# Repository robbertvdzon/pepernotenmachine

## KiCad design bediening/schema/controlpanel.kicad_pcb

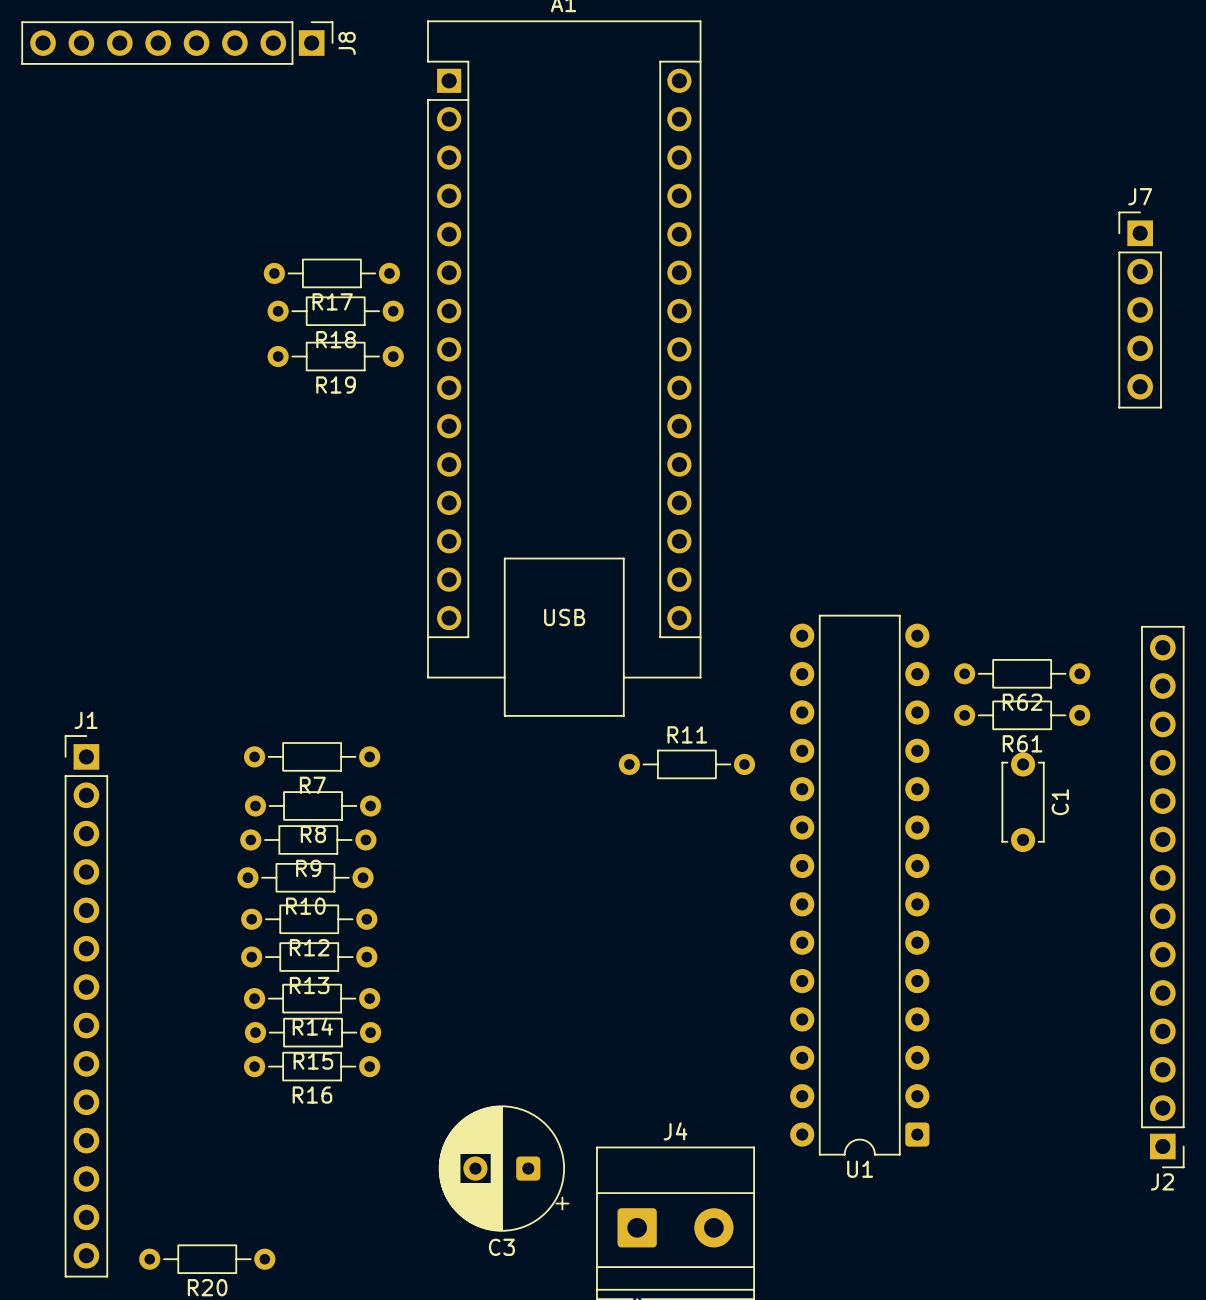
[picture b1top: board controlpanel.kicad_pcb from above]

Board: 2 copper layers, 25 parts (0 on the bottom side), 52 nets, no tracks yet.

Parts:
A1: Arduino_Nano_ESP32; Arduino_Nano
C1: 0.1uF; C_Disc_D5.0mm_W2.5mm_P5.00mm
C3: 470uF; CP_Radial_D8.0mm_P3.50mm
J1: Leds; PinHeader_1x14_P2.54mm_Vertical
J2: Schakelaars; PinHeader_1x14_P2.54mm_Vertical
J4: Power; TerminalBlock_Phoenix_MKDS-1,5-2-5.08_1x02_P5.08mm_Horizont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
J7: Rotary switch; PinHeader_1x05_P2.54mm_Vertical
J8: SPI Display; PinHeader_1x08_P2.54mm_Vertical
R7, R8, R9, R10, R12, R13, R14, R15, R16, R17, R18, R19, R20: 330; R_Axial_DIN0204_L3.6mm_D1.6mm_P7.62mm_Horizontal
R11: 10k; R_Axial_DIN0204_L3.6mm_D1.6mm_P7.62mm_Horizontal
R61, R62: 4k7; R_Axial_DIN0204_L3.6mm_D1.6mm_P7.62mm_Horizontal
U1: MCP23017x-x-SP; DIP-28_W7.62mm

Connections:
+3.3V: A1.17 (3V3), C1.2, R11.1, R61.1, R62.1, U1.9 (V_{DD})
+3V3: J1.13, J2.13, J7.2, J8.8
+5V: A1.30 (VIN), C3.1, J4.2, J8.2
/CS: A1.13 (D10/CS), J8.7
/DC: A1.12 (D9), J8.6
/DISPLAY_RESET: A1.11 (D8), J8.5
/L1: R7.1, U1.21 (GPA0)
/L2: R8.1, U1.22 (GPA1)
/L3: R9.1, U1.23 (GPA2)
/L4: R10.1, U1.24 (GPA3)
/L5: R12.1, U1.25 (GPA4)
/L6: R13.1, U1.26 (GPA5)
/L7: R14.1, U1.27 (GPA6)
/L8: R15.1, U1.28 (GPA7)
/L9: A1.5 (D2), R16.1
/L10: A1.6 (D3), R17.1
/L11: A1.7 (D4), R18.1
/L12: A1.8 (D5), R19.1
/MOSI: A1.14 (D11/COPI), J8.4
/ROT_CLK: A1.19 (A0), J7.4
/ROT_CT: A1.20 (A1), J7.5
/ROT_SW: A1.10 (D7), J7.3
/SCL: A1.24 (SCL/A5), R61.2, U1.12 (SCK)
/SCLK: A1.16 (D13/SCK), J8.3
/SDA: A1.23 (SDA/A4), R62.2, U1.13 (SDA)
/SW1: J2.1, U1.1 (GPB0)
/SW2: J2.2, U1.2 (GPB1)
/SW3: J2.3, U1.3 (GPB2)
/SW4: J2.4, U1.4 (GPB3)
/SW5: J2.5, U1.5 (GPB4)
/SW6: J2.6, U1.6 (GPB5)
/SW7: J2.7, U1.7 (GPB6)
/SW8: J2.8, U1.8 (GPB7)
/SW9: A1.21 (A2), J2.9
/SW10: A1.22 (A3), J2.10
/SW11: A1.25 (A6), J2.11
/SW12: A1.26 (A7), J2.12
GND: A1.4 (GND), A1.29 (GND), C1.1, C3.2, J2.14, J4.1, J7.1, J8.1, R20.1, U1.10 (V_{SS}), U1.15 (A0), U1.16 (A1), U1.17 (A2)
unnamed: J1.1, R7.2
unnamed: J1.2, R8.2
unnamed: J1.3, R9.2
unnamed: J1.4, R10.2
unnamed: J1.5, R12.2
unnamed: J1.6, R13.2
unnamed: J1.7, R14.2
unnamed: J1.8, R15.2
unnamed: J1.9, R16.2
unnamed: J1.10, R17.2
unnamed: J1.11, R18.2
unnamed: J1.12, R19.2
unnamed: J1.14, R20.2
unnamed: R11.2, U1.18 (~RESET)

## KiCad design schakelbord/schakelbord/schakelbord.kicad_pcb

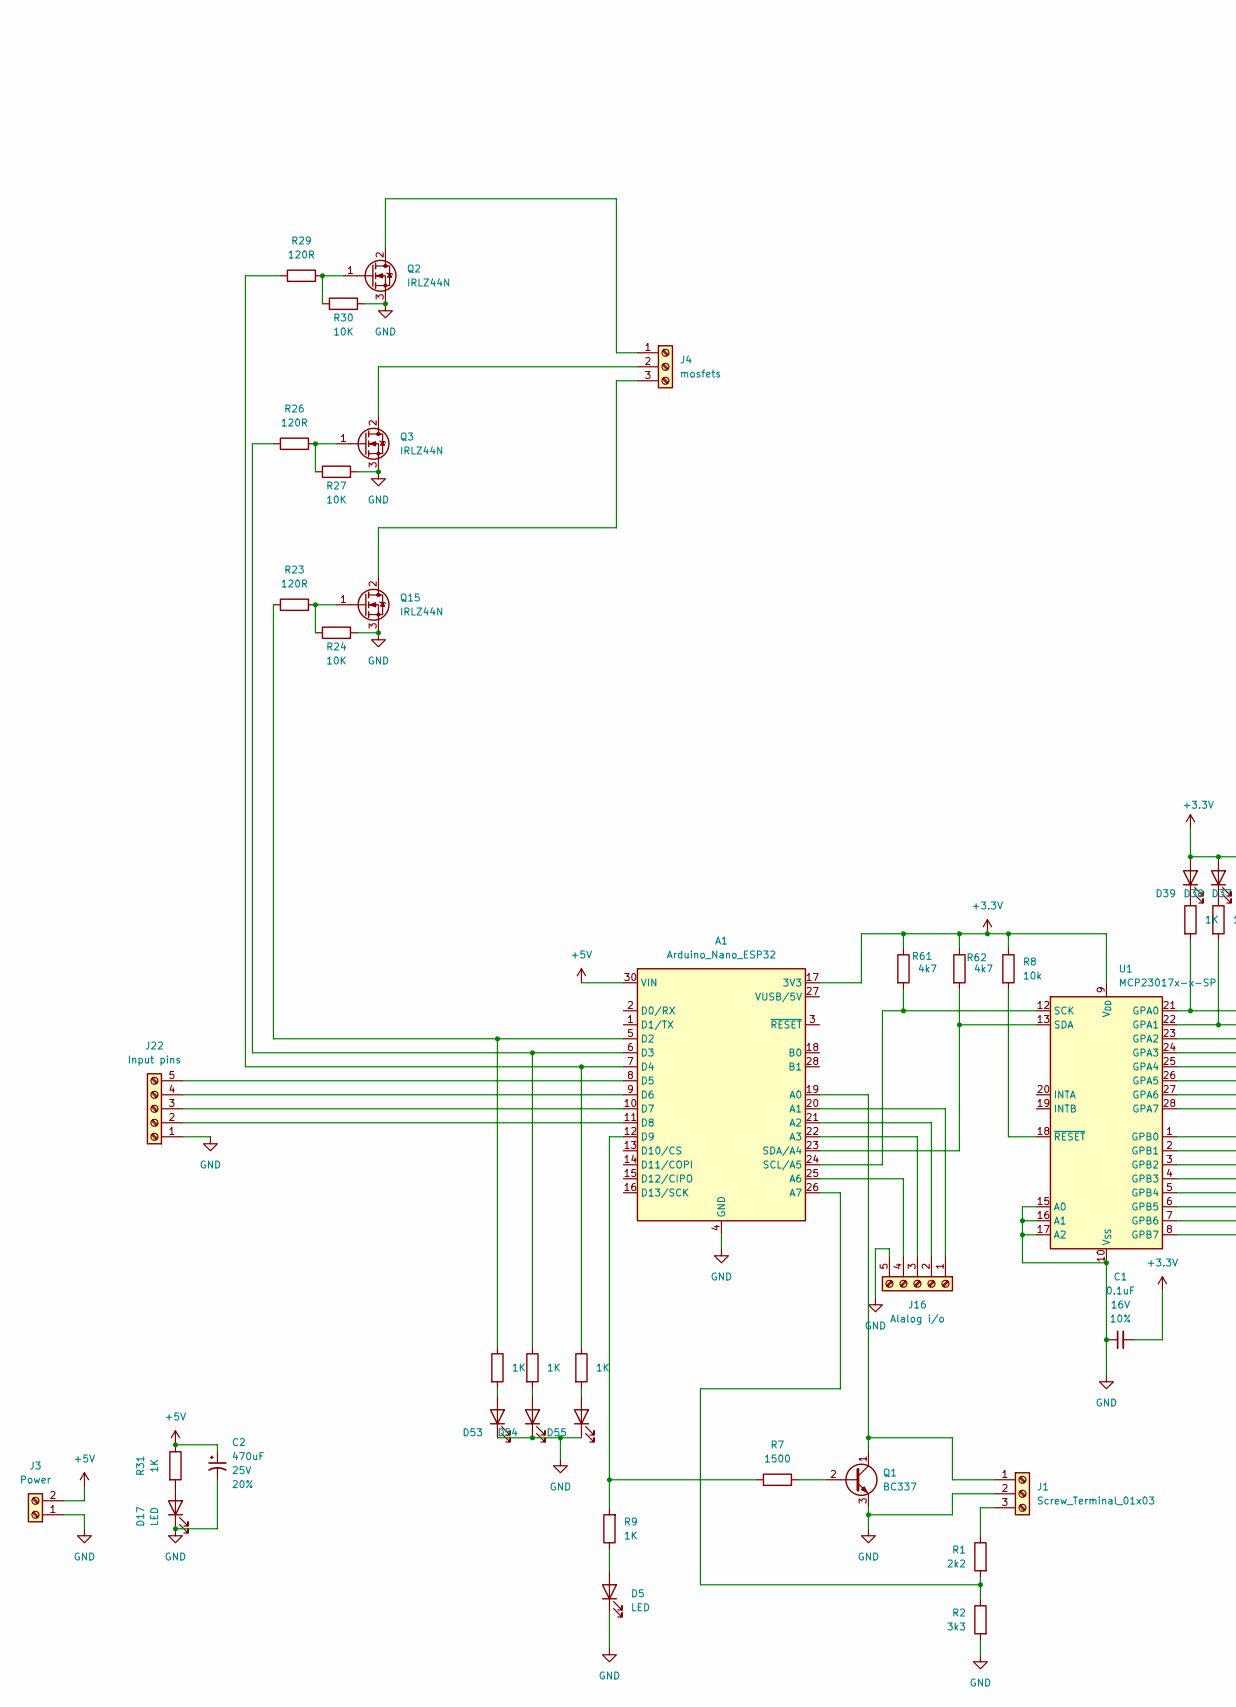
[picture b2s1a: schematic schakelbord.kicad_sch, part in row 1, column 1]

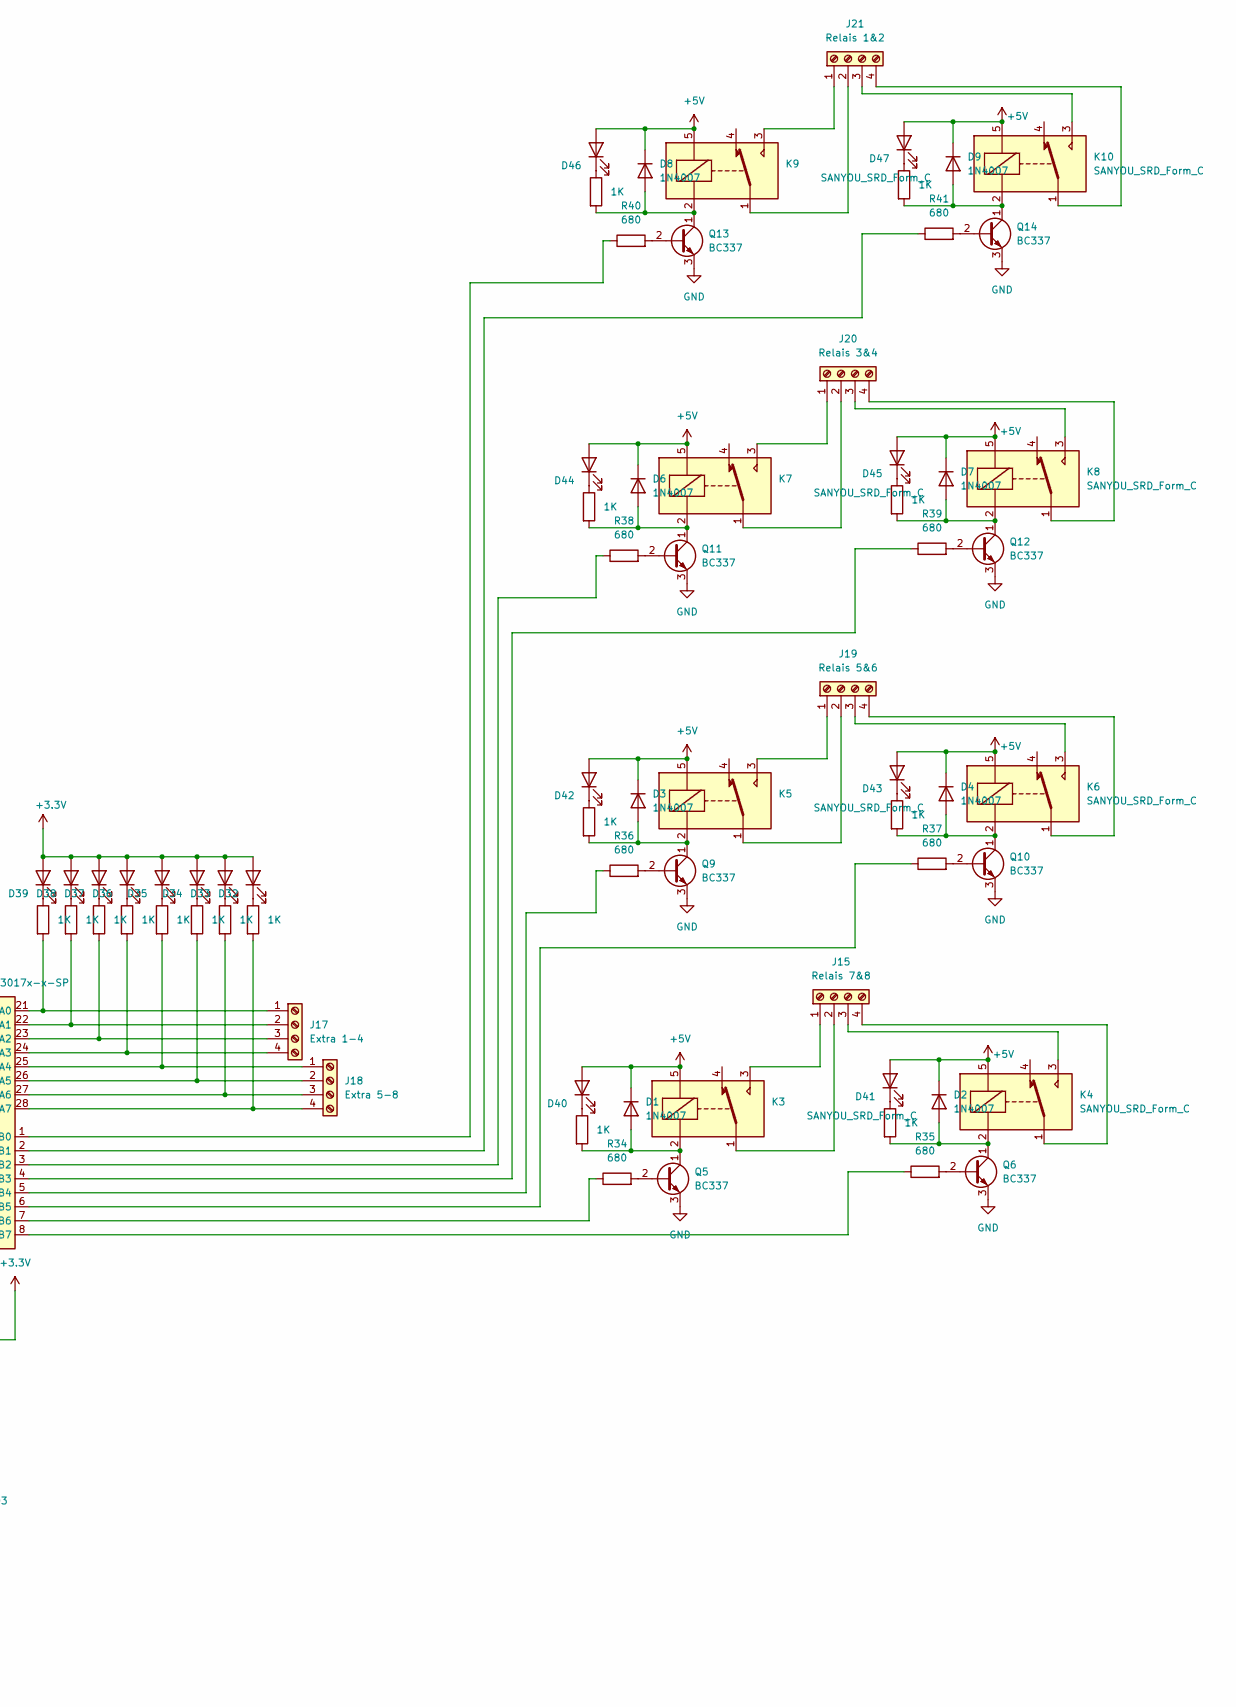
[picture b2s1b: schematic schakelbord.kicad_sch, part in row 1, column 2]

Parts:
A1: Arduino_Nano_ESP32; Arduino_Nano
C1: 0.1uF; C_Disc_D5.0mm_W2.5mm_P5.00mm; Voltage 16V; Tolerance 10%
C2: 470uF; CP_Radial_D8.0mm_P3.50mm; Voltage 25V; Tolerance 20%
D1, D2, D3, D4, D6, D7, D8, D9: 1N4007; D_DO-41_SOD81_P10.16mm_Horizontal
D5, D17, D32, D33, D34, D35, D36, D37, D38, D39, D40, D41, D42, D43, D44, D45, D46, D47, D53, D54, D55: LED; LED_D5.0mm
J1: Screw_Terminal_01x03; TerminalBlock_Phoenix_MKDS-1,5-3-5.08_1x03_P5.08mm_Horizont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
J3: Power; TerminalBlock_Phoenix_MKDS-1,5-2-5.08_1x02_P5.08mm_Horizont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
J4: mosfets; TerminalBlock_Phoenix_MKDS-1,5-3_1x03_P5.00mm_Horizontal
J15: Relais 7&8; TerminalBlock_Phoenix_MKDS-1,5-4-5.08_1x04_P5.08mm_Horizont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
J16: Alalog i/o; TerminalBlock_Phoenix_MKDS-1,5-5-5.08_1x05_P5.08mm_Horizont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
J17: Extra 1-4; TerminalBlock_Phoenix_MKDS-1,5-4-5.08_1x04_P5.08mm_Horizont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
J18: Extra 5-8; TerminalBlock_Phoenix_MKDS-1,5-4-5.08_1x04_P5.08mm_Horizont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
J19: Relais 5&6; TerminalBlock_Phoenix_MKDS-1,5-4-5.08_1x04_P5.08mm_Horizont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
J20: Relais 3&4; TerminalBlock_Phoenix_MKDS-1,5-4-5.08_1x04_P5.08mm_Horizont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
J21: Relais 1&2; TerminalBlock_Phoenix_MKDS-1,5-4-5.08_1x04_P5.08mm_Horizont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
J22: Input pins; TerminalBlock_Phoenix_MKDS-1,5-5-5.08_1x05_P5.08mm_Horizont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
K3, K4, K5, K6, K7, K8, K9, K10: SANYOU_SRD_Form_C; Relay_SPDT_SANYOU_SRD_Series_Form_C
Q1, Q5, Q6, Q9, Q10, Q11, Q12, Q13, Q14: BC337; TO-92L_Inline_Wide
Q2, Q3, Q15: IRLZ44N; TO-220-3_Vertical
R1: 2k2; R_Axial_DIN0204_L3.6mm_D1.6mm_P7.62mm_Horizontal
R2: 3k3; R_Axial_DIN0204_L3.6mm_D1.6mm_P7.62mm_Horizontal
R7: 1500; R_Axial_DIN0204_L3.6mm_D1.6mm_P7.62mm_Horizontal
R8: 10k; R_Axial_DIN0204_L3.6mm_D1.6mm_P7.62mm_Horizontal
R9: 1K; R_Axial_DIN0207_L6.3mm_D2.5mm_P10.16mm_Horizontal
R23, R26, R29: 120R; R_Axial_DIN0204_L3.6mm_D1.6mm_P7.62mm_Horizontal
R24, R27, R30: 10K; R_Axial_DIN0204_L3.6mm_D1.6mm_P7.62mm_Horizontal
R31, R44, R45, R46, R47, R48, R49, R50, R51, R52, R53, R54, R55, R56, R57, R58, R59, R67, R68, R69: 1K; R_Axial_DIN0204_L3.6mm_D1.6mm_P7.62mm_Horizontal
R34, R35, R36, R37, R38, R39, R40, R41: 680; R_Axial_DIN0204_L3.6mm_D1.6mm_P7.62mm_Horizontal
R61, R62: 4k7; R_Axial_DIN0204_L3.6mm_D1.6mm_P7.62mm_Horizontal
U1: MCP23017x-x-SP; DIP-28_W7.62mm

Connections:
+3.3V: A1.17 (3V3), C1.2, D32.2 (A), D33.2 (A), D34.2 (A), D35.2 (A), D36.2 (A), D37.2 (A), D38.2 (A), D39.2 (A), R8.1, R61.1, R62.1, U1.9 (V_{DD})
+5V: A1.30 (VIN), C2.1, D1.1 (K), D2.1 (K), D3.1 (K), D4.1 (K), D6.1 (K), D7.1 (K), D8.1 (K), D9.1 (K), D40.2 (A), D41.2 (A), D42.2 (A), D43.2 (A), D44.2 (A), D45.2 (A), D46.2 (A), D47.2 (A), J3.2, K3.5, K4.5, K5.5, K6.5, K7.5, K8.5, K9.5, K10.5, R31.1
GND: A1.4 (GND), A1.29 (GND), C1.1, C2.2, D5.1 (K), D17.1 (K), D53.1 (K), D54.1 (K), D55.1 (K), J1.2, J3.1, J16.5, J22.1, Q1.3 (E), Q2.3 (S), Q3.3 (S), Q5.3 (E), Q6.3 (E), Q9.3 (E), Q10.3 (E), Q11.3 (E), Q12.3 (E), Q13.3 (E), Q14.3 (E), Q15.3 (S), R2.2, R24.2, R27.2, R30.2, U1.10 (V_{SS}), U1.15 (A0), U1.16 (A1), U1.17 (A2)
unnamed: A1.19 (A0), J1.1, Q1.1 (C)
unnamed: A1.20 (A1), J16.1
unnamed: A1.21 (A2), J16.2
unnamed: A1.22 (A3), J16.3
unnamed: A1.25 (A6), J16.4
unnamed: A1.26 (A7), R1.2, R2.1
unnamed: A1.5 (D2), R23.1, R67.1
unnamed: A1.6 (D3), R26.1, R68.1
unnamed: A1.7 (D4), R29.1, R69.1
unnamed: A1.8 (D5), J22.5
unnamed: A1.9 (D6), J22.4
unnamed: A1.10 (D7), J22.3
unnamed: A1.11 (D8), J22.2
unnamed: A1.12 (D9), R7.1, R9.2
unnamed: A1.24 (SCL/A5), R61.2, U1.12 (SCK)
unnamed: A1.23 (SDA/A4), R62.2, U1.13 (SDA)
unnamed: D1.2 (A), K3.2, Q5.1 (C), R52.2
unnamed: D2.2 (A), K4.2, Q6.1 (C), R53.2
unnamed: D3.2 (A), K5.2, Q9.1 (C), R54.2
unnamed: D4.2 (A), K6.2, Q10.1 (C), R55.2
unnamed: D5.2 (A), R9.1
unnamed: D6.2 (A), K7.2, Q11.1 (C), R56.2
unnamed: D7.2 (A), K8.2, Q12.1 (C), R57.2
unnamed: D8.2 (A), K9.2, Q13.1 (C), R58.2
unnamed: D9.2 (A), K10.2, Q14.1 (C), R59.2
unnamed: D17.2 (A), R31.2
unnamed: D32.1 (K), R51.1
unnamed: D33.1 (K), R50.1
unnamed: D34.1 (K), R49.1
unnamed: D35.1 (K), R48.1
unnamed: D36.1 (K), R47.1
unnamed: D37.1 (K), R46.1
unnamed: D38.1 (K), R45.1
unnamed: D39.1 (K), R44.1
unnamed: D40.1 (K), R52.1
unnamed: D41.1 (K), R53.1
unnamed: D42.1 (K), R54.1
unnamed: D43.1 (K), R55.1
unnamed: D44.1 (K), R56.1
unnamed: D45.1 (K), R57.1
unnamed: D46.1 (K), R58.1
unnamed: D47.1 (K), R59.1
unnamed: D53.2 (A), R67.2
unnamed: D54.2 (A), R68.2
unnamed: D55.2 (A), R69.2
unnamed: J1.3, R1.1
unnamed: J4.1, Q2.2 (D)
unnamed: J4.2, Q3.2 (D)
unnamed: J4.3, Q15.2 (D)
unnamed: J15.1, K3.3
unnamed: J15.2, K3.1
unnamed: J15.3, K4.3
unnamed: J15.4, K4.1
unnamed: J17.1, R44.2, U1.21 (GPA0)
unnamed: J17.2, R45.2, U1.22 (GPA1)
unnamed: J17.3, R46.2, U1.23 (GPA2)
unnamed: J17.4, R47.2, U1.24 (GPA3)
unnamed: J18.1, R48.2, U1.25 (GPA4)
unnamed: J18.2, R49.2, U1.26 (GPA5)
unnamed: J18.3, R50.2, U1.27 (GPA6)
unnamed: J18.4, R51.2, U1.28 (GPA7)
unnamed: J19.1, K5.3
unnamed: J19.2, K5.1
unnamed: J19.3, K6.3
unnamed: J19.4, K6.1
unnamed: J20.1, K7.3
unnamed: J20.2, K7.1
unnamed: J20.3, K8.3
unnamed: J20.4, K8.1
unnamed: J21.1, K9.3
unnamed: J21.2, K9.1
unnamed: J21.3, K10.3
unnamed: J21.4, K10.1
unnamed: Q1.2 (B), R7.2
unnamed: Q2.1 (G), R29.2, R30.1
unnamed: Q3.1 (G), R26.2, R27.1
unnamed: Q5.2 (B), R34.2
unnamed: Q6.2 (B), R35.2
unnamed: Q9.2 (B), R36.2
unnamed: Q10.2 (B), R37.2
unnamed: Q11.2 (B), R38.2
unnamed: Q12.2 (B), R39.2
unnamed: Q13.2 (B), R40.2
unnamed: Q14.2 (B), R41.2
unnamed: Q15.1 (G), R23.2, R24.1
unnamed: R40.1, U1.1 (GPB0)
unnamed: R41.1, U1.2 (GPB1)
unnamed: R38.1, U1.3 (GPB2)
unnamed: R39.1, U1.4 (GPB3)
unnamed: R36.1, U1.5 (GPB4)
unnamed: R37.1, U1.6 (GPB5)
unnamed: R34.1, U1.7 (GPB6)
unnamed: R35.1, U1.8 (GPB7)
unnamed: R8.2, U1.18 (~RESET)

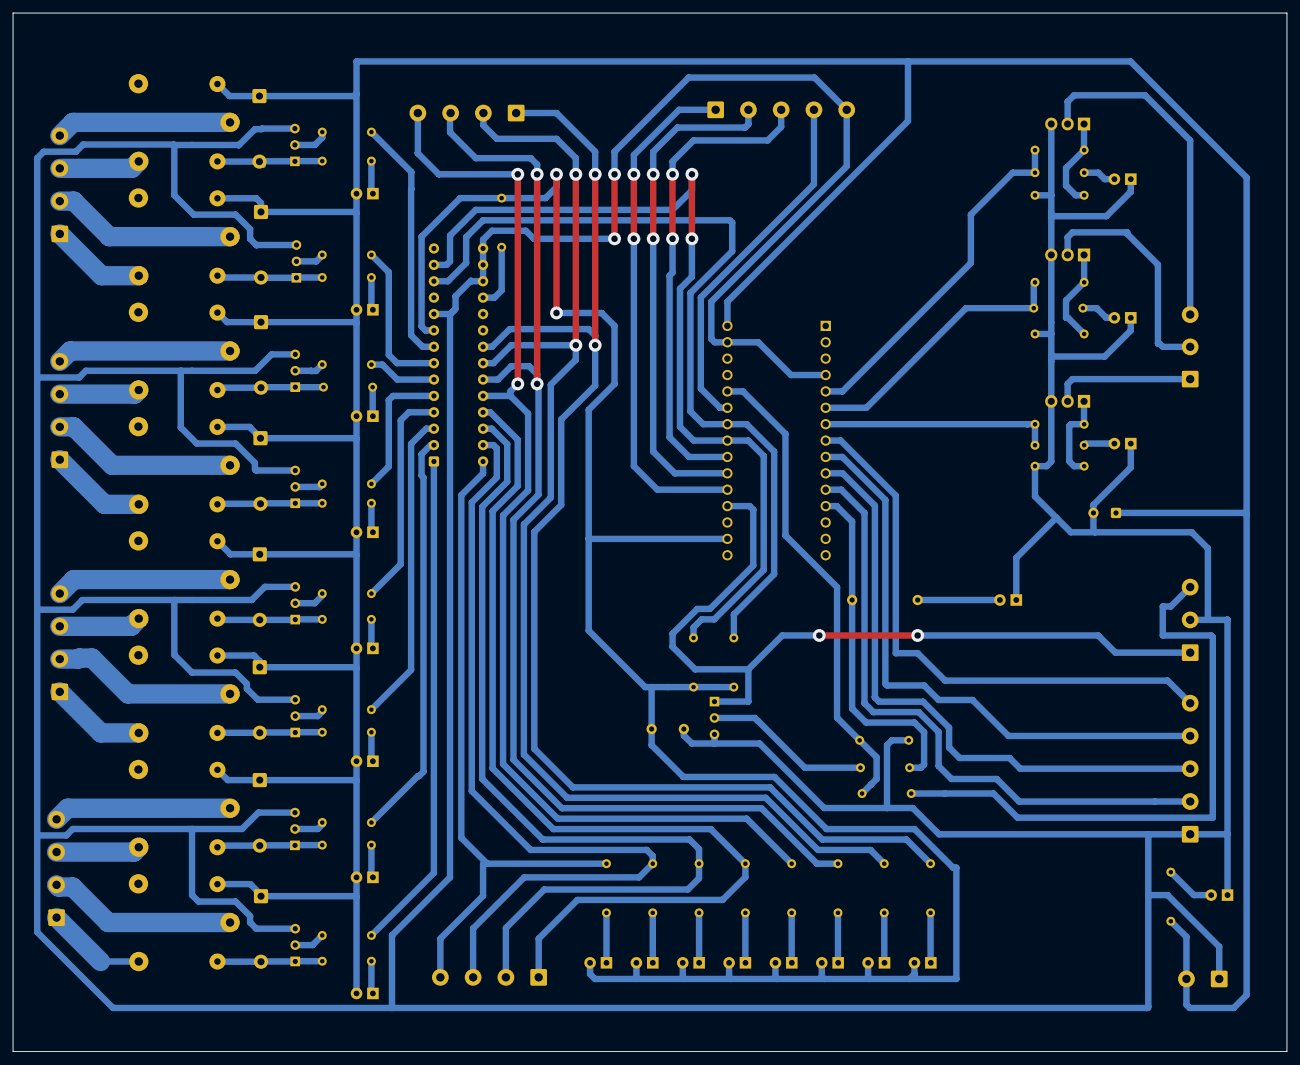
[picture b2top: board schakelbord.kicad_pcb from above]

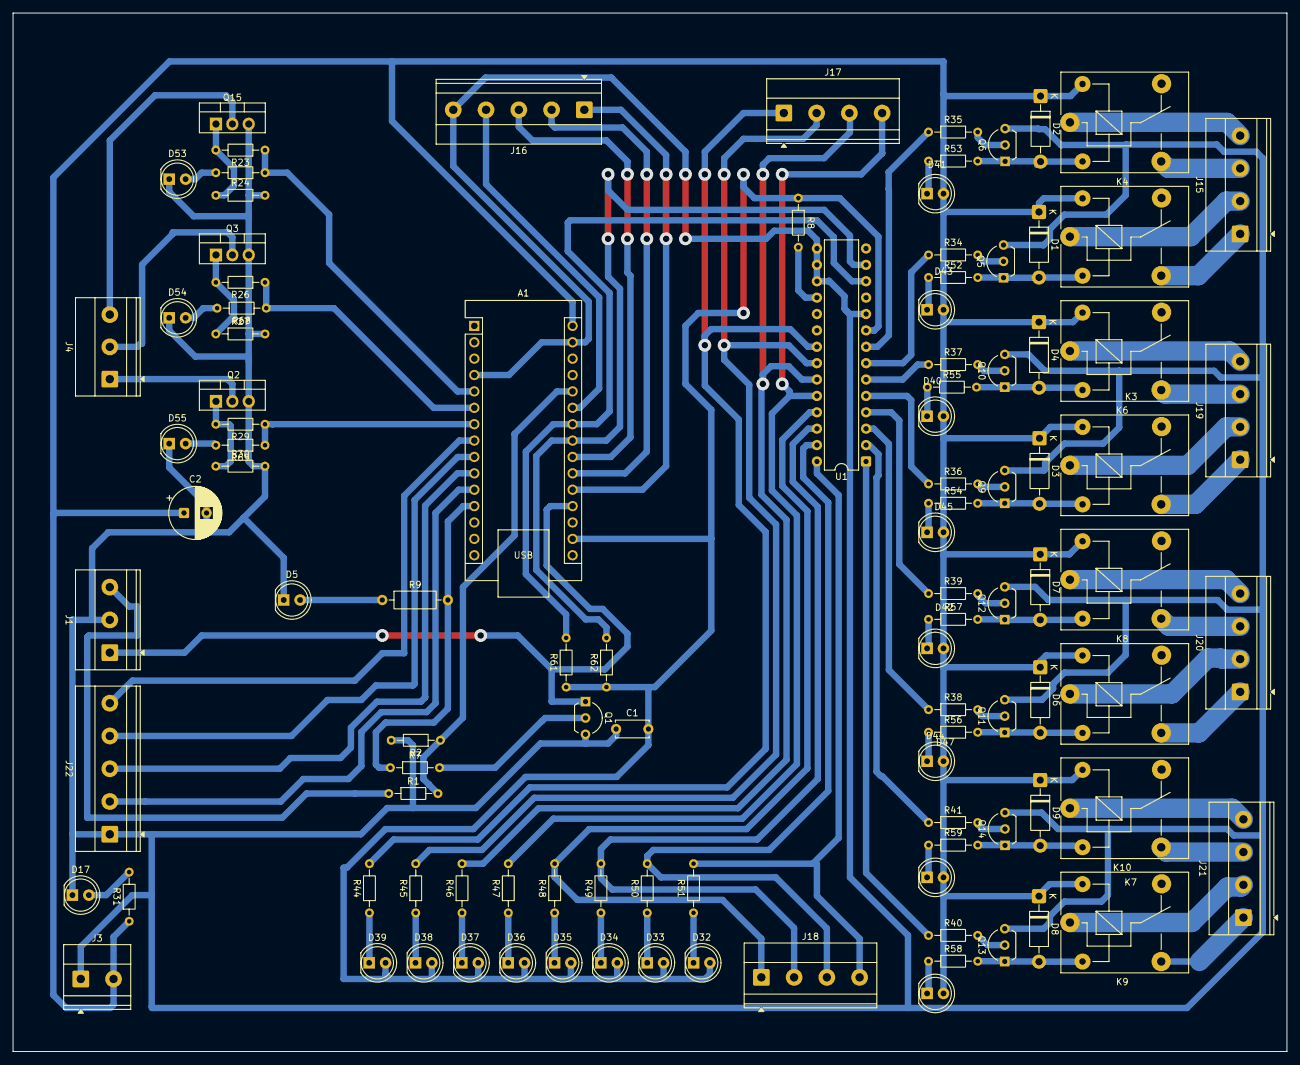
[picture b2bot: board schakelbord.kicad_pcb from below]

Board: 2 copper layers, 197.5 x 161.0 mm, 105 parts (105 on the bottom side), 97 nets.

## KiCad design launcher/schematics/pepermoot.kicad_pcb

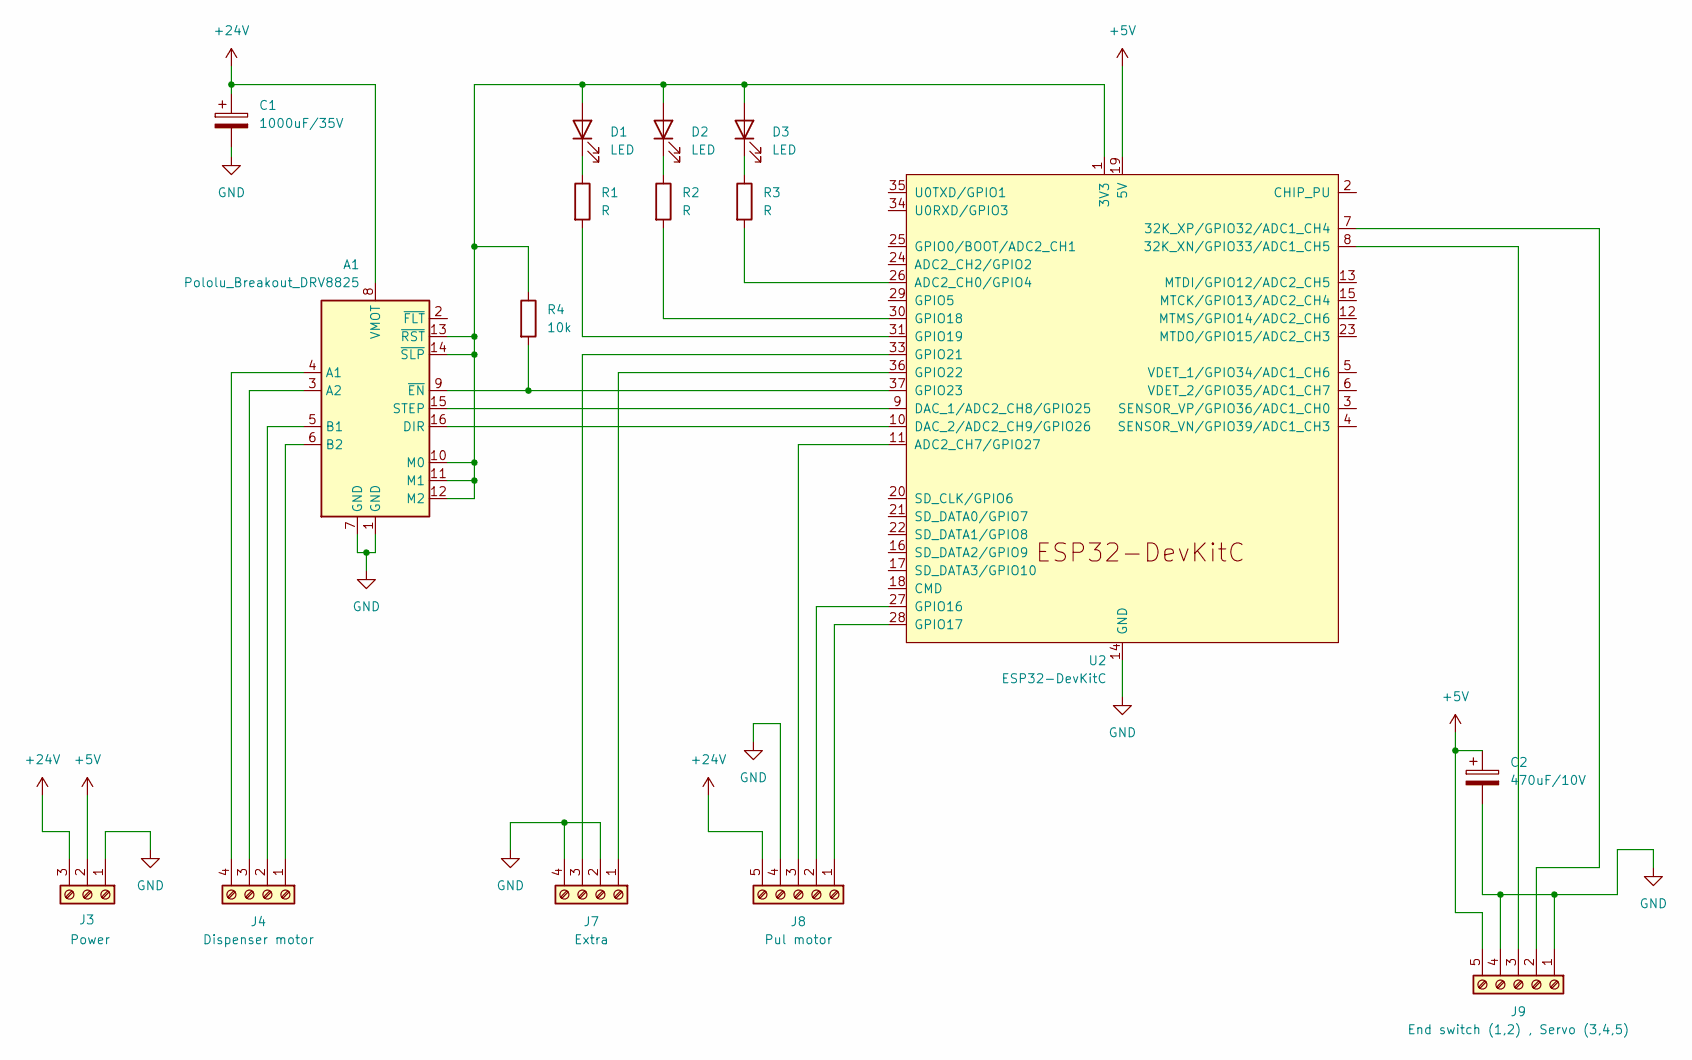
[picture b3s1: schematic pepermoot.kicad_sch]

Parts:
A1: Pololu_Breakout_DRV8825; Pololu_Breakout-16_15.2x20.3mm
C1: 1000uF/35V; CP_Radial_D10.0mm_P5.00mm
C2: 470uF/10V; CP_Radial_D10.0mm_P5.00mm
D1, D2, D3: LED; LED_D5.0mm
J3: Power; TerminalBlock_Phoenix_MKDS-1,5-3-5.08_1x03_P5.08mm_Horizont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
J4: Dispenser motor; TerminalBlock_Phoenix_MKDS-1,5-4-5.08_1x04_P5.08mm_Horizont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
J7: Extra; TerminalBlock_Phoenix_MKDS-1,5-4-5.08_1x04_P5.08mm_Horizont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
J8: Pul motor; TerminalBlock_Phoenix_MKDS-1,5-5-5.08_1x05_P5.08mm_Horizont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
J9: End switch (1,2) , Servo (3,4,5); TerminalBlock_Phoenix_MKDS-1,5-5-5.08_1x05_P5.08mm_Horizont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
R1, R2, R3: R; R_Axial_DIN0207_L6.3mm_D2.5mm_P10.16mm_Horizontal
R4: 10k; R_Axial_DIN0204_L3.6mm_D1.6mm_P7.62mm_Horizontal
U2: ESP32-DevKitC

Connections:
+5V: C2.1, J3.2, J9.5, U2.19 (5V)
+24V: A1.8 (VMOT), C1.1, J3.3, J8.5
GND: A1.1 (GND), A1.7 (GND), C1.2, C2.2, J3.1, J7.2, J7.4, J8.4, J9.1, J9.4, U2.14 (GND), U2.32 (GND), U2.38 (GND)
unnamed: A1.4 (A1), J4.4
unnamed: A1.3 (A2), J4.3
unnamed: A1.5 (B1), J4.2
unnamed: A1.6 (B2), J4.1
unnamed: A1.16 (DIR), U2.10 (DAC_2/ADC2_CH9/GPIO26)
unnamed: A1.10 (M0), A1.11 (M1), A1.12 (M2), A1.13 (~RST), A1.14 (~SLP), D1.2 (A), D2.2 (A), D3.2 (A), R4.1, U2.1 (3V3)
unnamed: A1.15 (STEP), U2.9 (DAC_1/ADC2_CH8/GPIO25)
unnamed: A1.9 (~EN), R4.2, U2.37 (GPIO23)
unnamed: D1.1 (K), R1.1
unnamed: D2.1 (K), R2.1
unnamed: D3.1 (K), R3.1
unnamed: J7.1, U2.36 (GPIO22)
unnamed: J7.3, U2.33 (GPIO21)
unnamed: J8.1, U2.28 (GPIO17)
unnamed: J8.2, U2.27 (GPIO16)
unnamed: J8.3, U2.11 (ADC2_CH7/GPIO27)
unnamed: J9.2, U2.7 (32K_XP/GPIO32/ADC1_CH4)
unnamed: J9.3, U2.8 (32K_XN/GPIO33/ADC1_CH5)
unnamed: R3.2, U2.26 (ADC2_CH0/GPIO4)
unnamed: R2.2, U2.30 (GPIO18)
unnamed: R1.2, U2.31 (GPIO19)

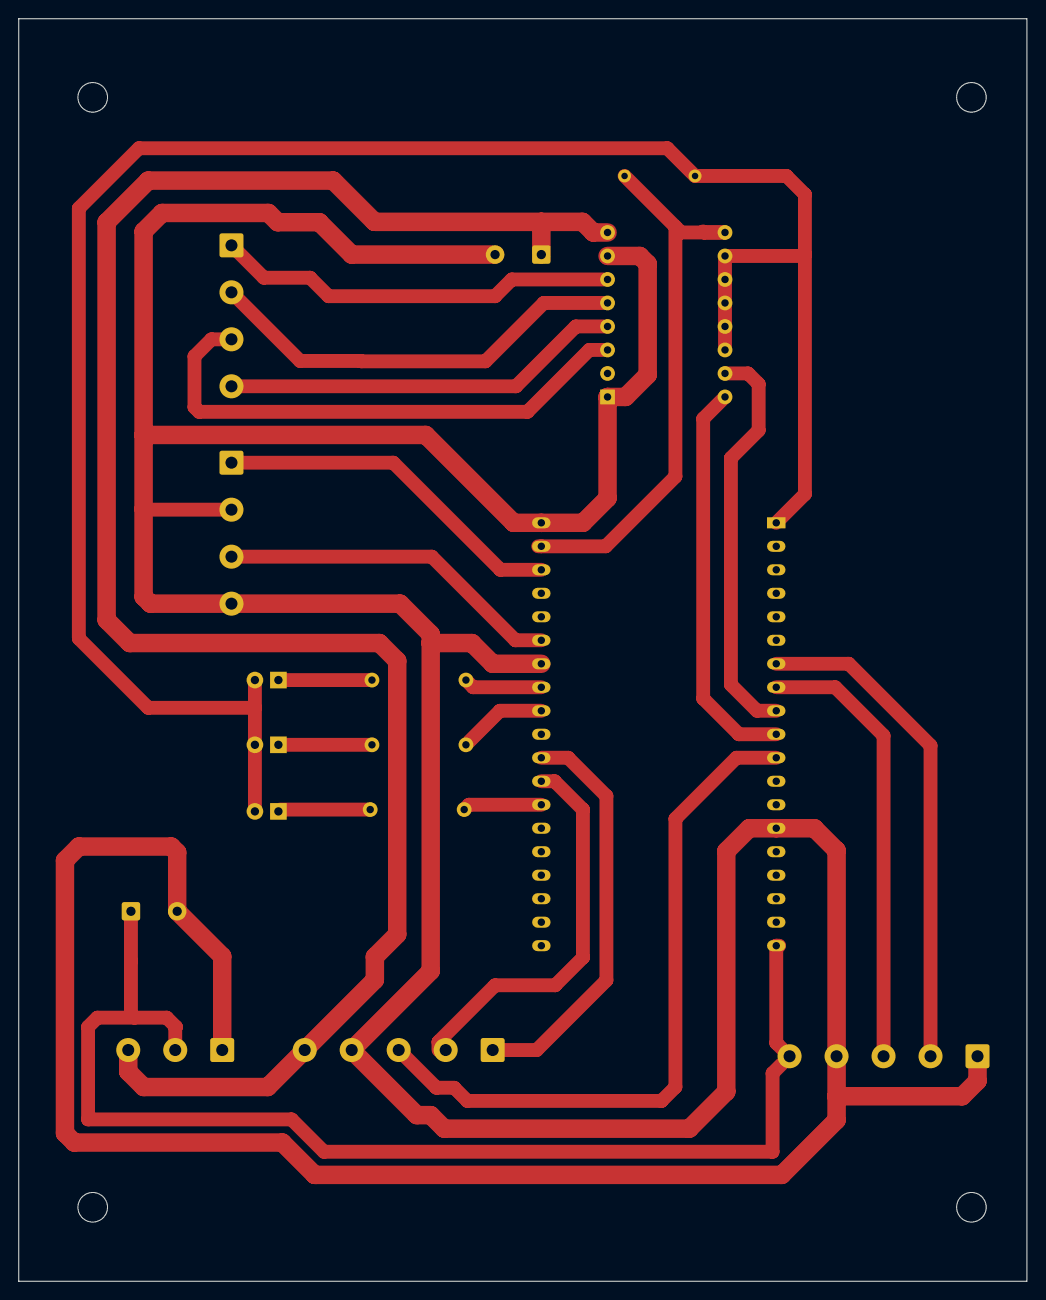
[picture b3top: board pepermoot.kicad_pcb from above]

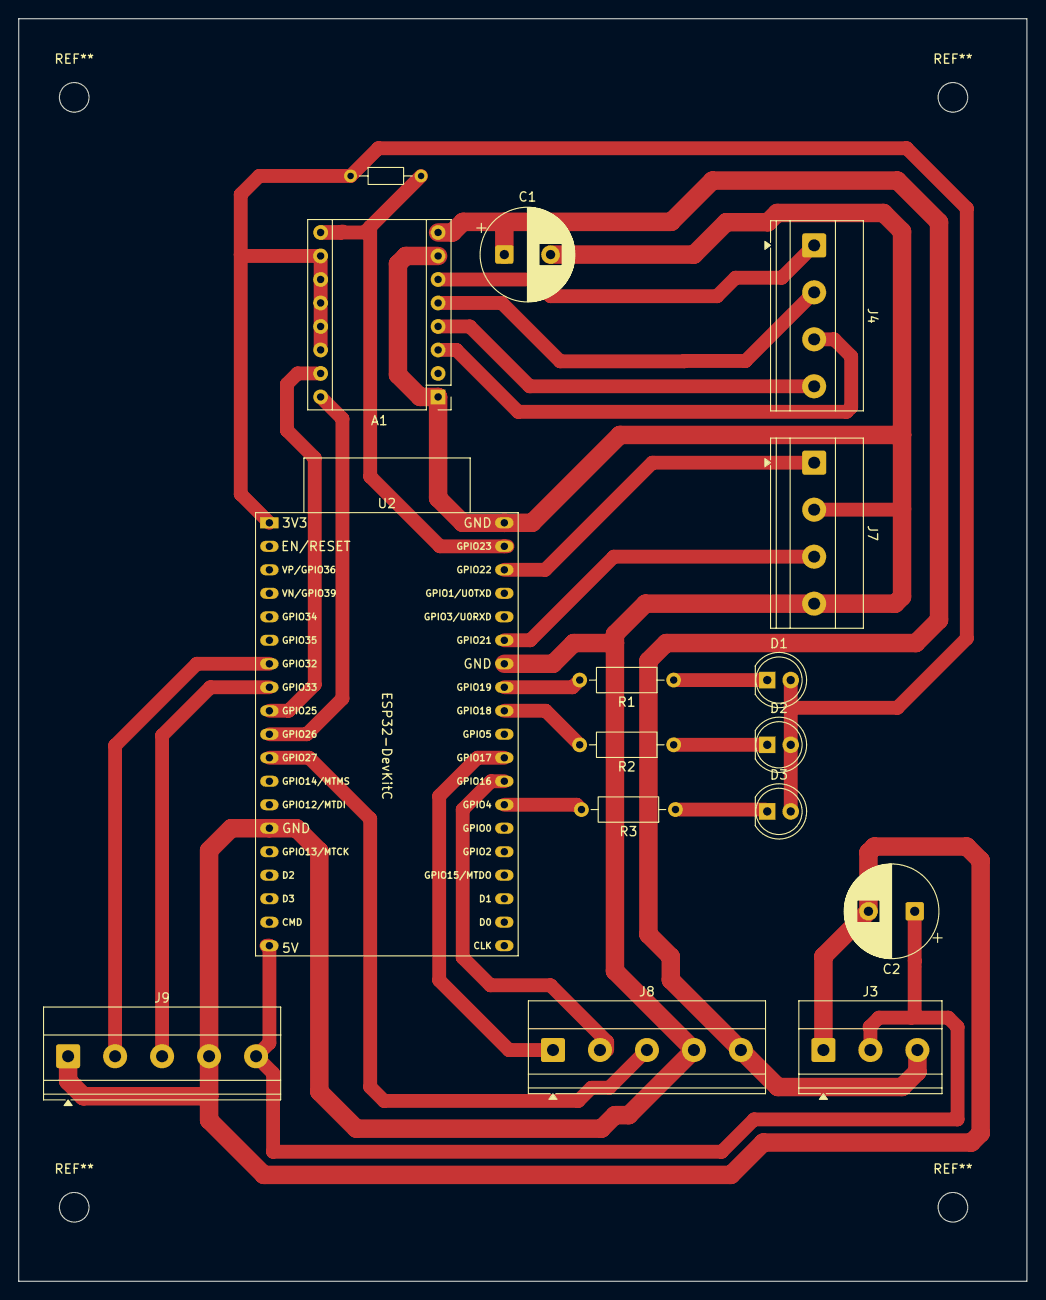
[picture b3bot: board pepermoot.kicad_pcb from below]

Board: 2 copper layers, 109.0 x 136.5 mm, 16 parts (16 on the bottom side), 24 nets.

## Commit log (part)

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2026-01-07 Restructure the code
2026-01-07 Extract horn code
2026-01-07 Add option to control a neo-pixel
2026-01-08 Move from the Expresif BLE implementation to NIMBLE (to reduce the flash file size)
2026-01-15 Add crossfade end indicator and add ability to control motor direction
2026-02-18 Drive the onboard NeoPixel of the Feather
2026-02-18 Provide linear motor speed control
2026-02-18 Make button code async
2026-02-18 Make horn code async
2026-02-18 Make the led code async
2026-02-18 Allow mulitple clients to connect
2026-03-27 Add characteristic that starts the launch routine
2026-04-10 Fix PWM timing conflict between servo and motor
